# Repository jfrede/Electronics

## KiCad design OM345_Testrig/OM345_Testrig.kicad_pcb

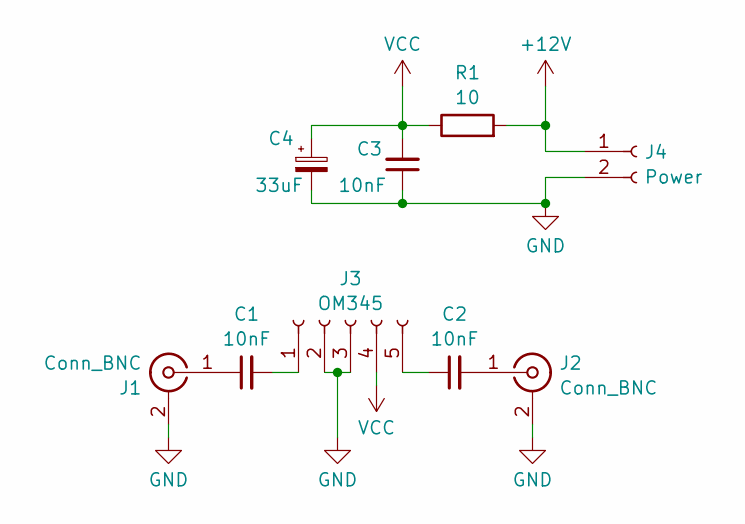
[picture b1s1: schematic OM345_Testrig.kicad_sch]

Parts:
C1, C2, C3: 10nF; C_0805_2012Metric_Pad1.18x1.45mm_HandSolder
C4: 33uF; CP_Radial_D5.0mm_P2.50mm
J1, J2: Conn_BNC; BNC_Amphenol_B6252HB-NPP3G-50_Horizontal
J3: OM345; PinSocket_1x05_P2.54mm_Vertical
J4: Power; PinHeader_1x02_P2.54mm_Vertical
R1: 10; R_0805_2012Metric_Pad1.20x1.40mm_HandSolder

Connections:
+12V: J4.1, R1.2
GND: C3.1, C4.2, J1.2 (Ext), J2.2 (Ext), J3.2, J3.3, J4.2
unnamed: C1.1, J1.1 (In)
unnamed: C2.2, J2.1 (In)
unnamed: C1.2, J3.1
unnamed: C2.1, J3.5
VCC: C3.2, C4.1, J3.4, R1.1

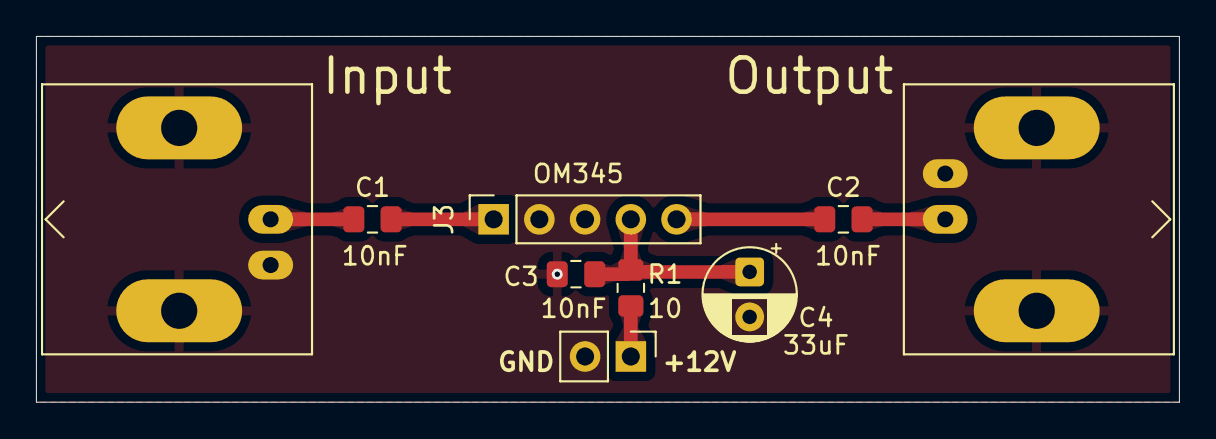
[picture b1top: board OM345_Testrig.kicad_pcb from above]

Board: 2 copper layers, 63.5 x 20.3 mm, 9 parts (0 on the bottom side), 7 nets.

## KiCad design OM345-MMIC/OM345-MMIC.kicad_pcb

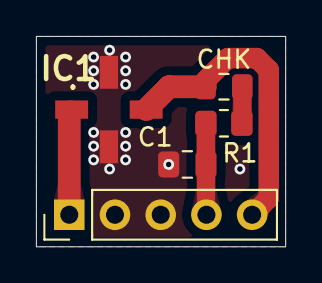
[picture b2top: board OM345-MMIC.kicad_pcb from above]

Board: 2 copper layers, 13.8 x 11.7 mm, 5 parts (0 on the bottom side), 5 nets.

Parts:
C1: 100n; C_0805_2012Metric_Pad1.18x1.45mm_HandSolder
CHK: 1k; L_0805_2012Metric_Pad1.15x1.40mm_HandSolder
IC1: MAR-7SM+; MAR7SM
J1: Conn_01x05_Pin; PinHeader_1x05_P2.54mm_Vertical
R1: 340; R_0805_2012Metric_Pad1.20x1.40mm_HandSolder

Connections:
GND: C1.1, IC1.2 (GND_1), IC1.4 (GND_2), J1.2, J1.3
unnamed: CHK.1, R1.2
unnamed: CHK.2, IC1.3 (RF-OUT_AND_DC-IN), J1.5
unnamed: IC1.1 (RF_IN), J1.1
unnamed: C1.2, J1.4, R1.1

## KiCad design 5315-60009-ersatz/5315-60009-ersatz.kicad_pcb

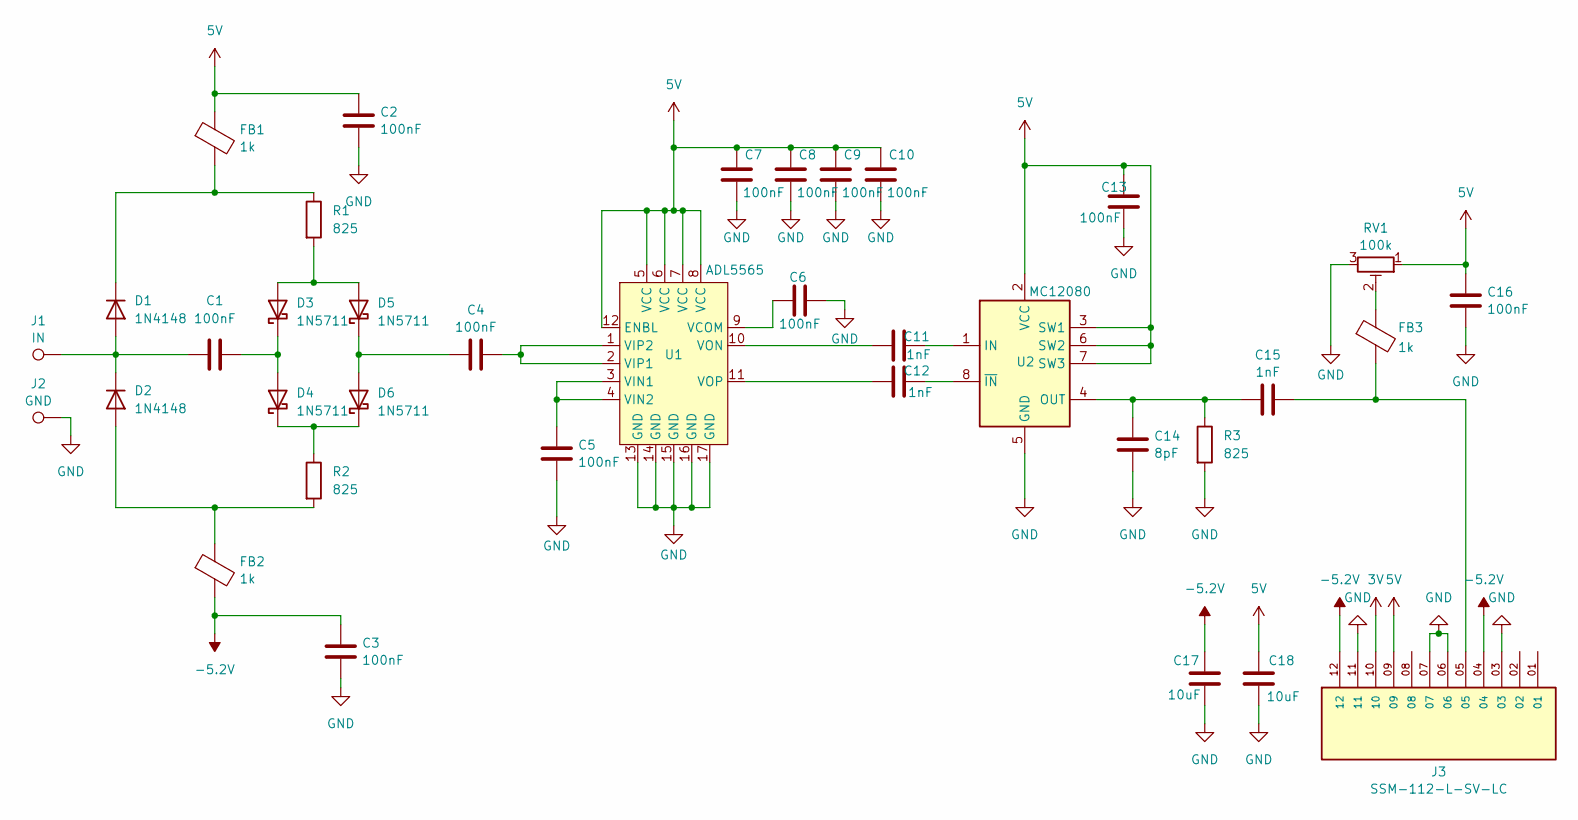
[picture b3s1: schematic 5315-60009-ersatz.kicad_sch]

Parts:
C1, C2, C3, C4, C5, C6, C7, C8, C9, C10, C13, C16: 100nF; C_0805_2012Metric
C11, C12, C15: 1nF; C_0805_2012Metric
C14: 8pF; C_0805_2012Metric
C17, C18: 10uF; R_1210_3225Metric
D1, D2: 1N4148; D_SOD-123F
D3, D4, D5, D6: 1N5711; D_SOD-123F
FB1, FB2, FB3: 1k; L_0805_2012Metric
J1: IN; TestPoint_Loop_D2.50mm_Drill1.0mm
J2: GND; TestPoint_Bridge_Pitch2.54mm_Drill1.0mm
J3: SSM-112-L-SV-LC; SAMTEC_SSM-112-L-SV-LC
R1, R2, R3: 825; R_0805_2012Metric
RV1: 100k; Potentiometer_Bourns_3314G_Vertical
U1: ADL5565; LFCSP-16-1EP_3x3mm_P0.5mm_EP1.6x1.6mm_ThermalVias
U2: MC12080; SOIC-8_3.9x4.9mm_P1.27mm

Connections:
3V: J3.10
5V: C2.1, C7.1, C8.1, C9.1, C10.1, C13.1, C16.1, C18.1, FB1.1, J3.09, RV1.1, U1.5 (VCC), U1.6 (VCC), U1.7 (VCC), U1.8 (VCC), U1.12 (ENBL), U2.2 (VCC), U2.3 (SW1), U2.6 (SW2), U2.7 (SW3)
-5.2V: C3.1, C17.1, FB2.2, J3.04, J3.12
GND: C2.2, C3.2, C5.2, C6.2, C7.2, C8.2, C9.2, C10.2, C13.2, C14.2, C16.2, C17.2, C18.2, J2.1, J3.03, J3.06, J3.07, J3.11, R3.2, RV1.3, U1.13 (GND), U1.14 (GND), U1.15 (GND), U1.16 (GND), U1.17 (GND), U2.5 (GND); also elsewhere on the board
unnamed: C15.2, FB3.2, J3.05
unnamed: C1.1, D1.2 (A), D2.1 (K), J1.1
unnamed: D1.1 (K), FB1.2, R1.1
unnamed: D2.2 (A), FB2.1, R2.2
unnamed: D3.2 (A), D5.2 (A), R1.2
unnamed: C1.2, D3.1 (K), D4.2 (A)
unnamed: D4.1 (K), D6.1 (K), R2.1
unnamed: C4.1, D5.1 (K), D6.2 (A)
unnamed 12: FB3.1, RV1.2; also elsewhere on the board
unnamed: C6.1, U1.9 (VCOM)
unnamed: C5.1, U1.3 (VIN1), U1.4 (VIN2)
unnamed: C4.2, U1.1 (VIP2), U1.2 (VIP1)
unnamed: C11.1, U1.10 (VON)
unnamed: C12.1, U1.11 (VOP)
unnamed: C11.2, U2.1 (IN)
unnamed: C14.1, C15.1, R3.1, U2.4 (OUT)
unnamed: C12.2, U2.8 (~IN)

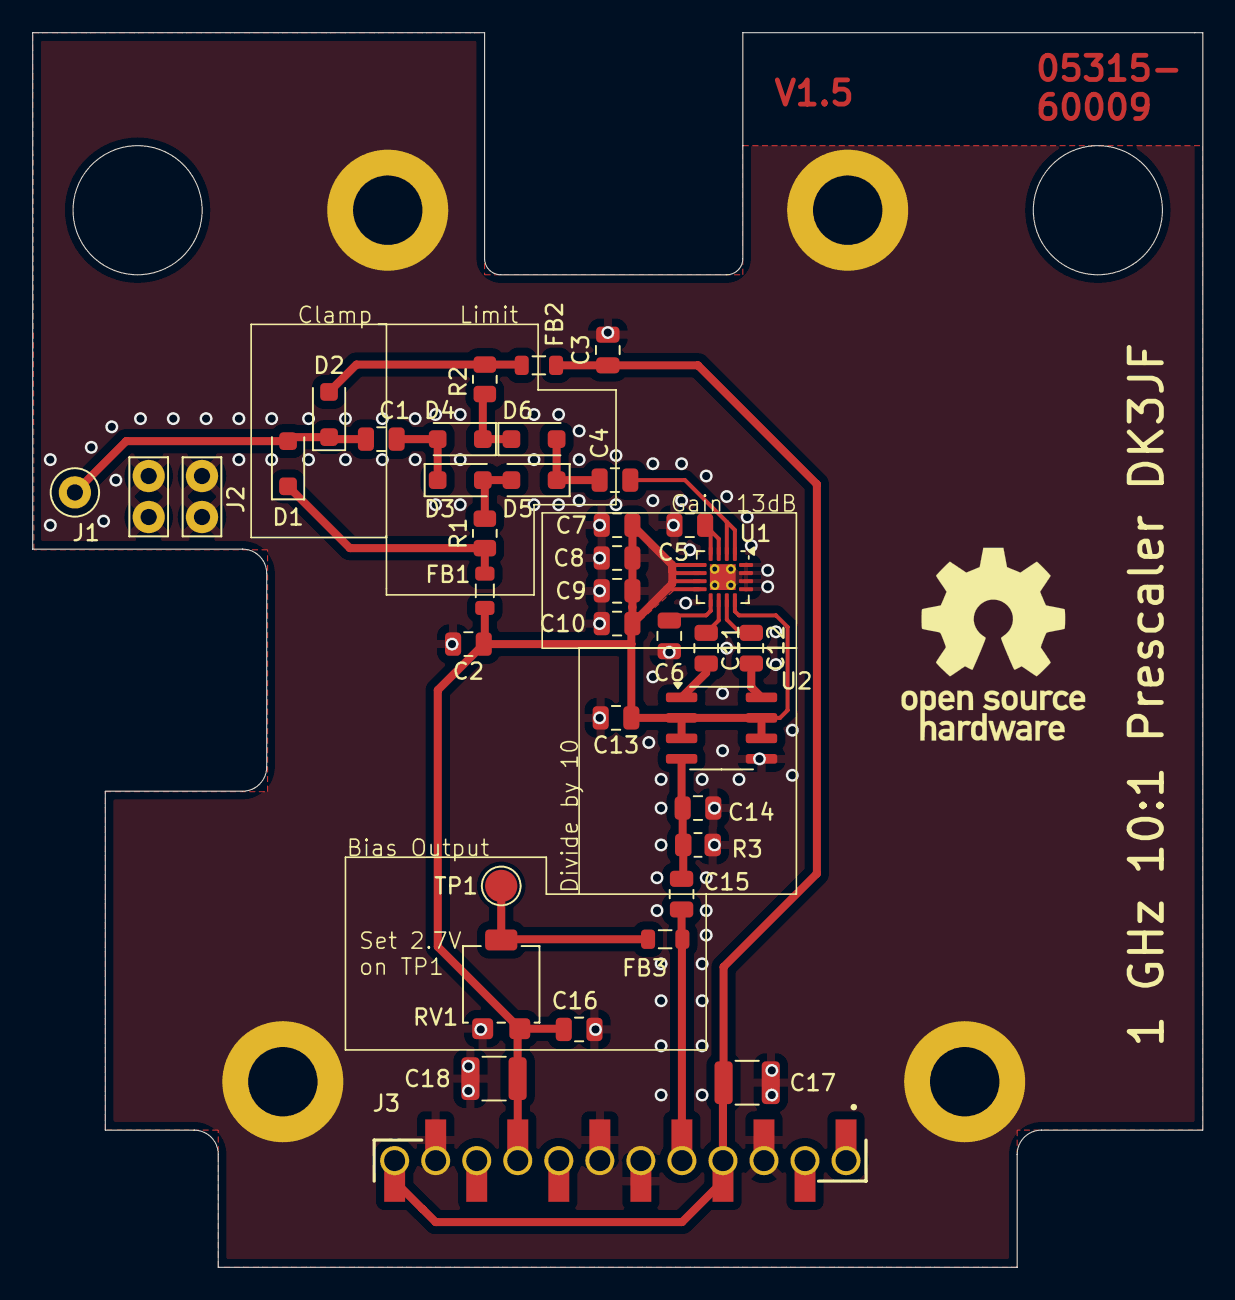
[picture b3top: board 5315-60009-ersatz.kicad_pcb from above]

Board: 2 copper layers, 72.5 x 76.5 mm, 38 parts (0 on the bottom side), 20 nets.

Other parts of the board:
J2#2: GND; TestPoint_Bridge_Pitch2.54mm_Drill1.0mm
TP1: TestPoint_Pad_D2.0mm

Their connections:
GND: J2#2.1; also elsewhere on the board
unnamed 12: TP1.1; also elsewhere on the board

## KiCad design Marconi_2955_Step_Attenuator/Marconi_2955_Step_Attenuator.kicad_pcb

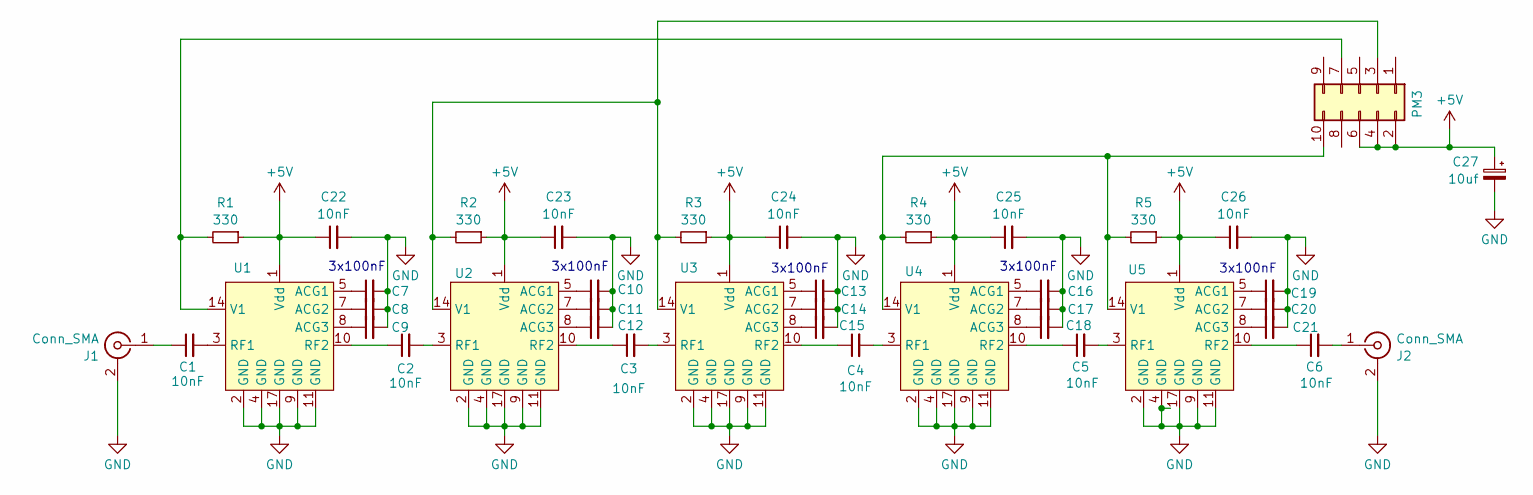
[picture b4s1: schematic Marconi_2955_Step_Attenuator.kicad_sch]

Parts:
C1, C2, C3, C4, C5, C6, C22, C23, C24, C25, C26: 10nF; C_0603_1608Metric
C7, C8, C9, C10, C11, C12, C13, C14, C15, C16, C17, C18, C19, C20, C21: 100nF; C_0603_1608Metric
C27: 10uf; CP_Radial_D6.3mm_P2.50mm
J1, J2: Conn_SMA; SMA_Wurth_60312002114503_Vertical
J3: PM3; PinHeader_2x05_P2.54mm_Vertical
R1, R2, R3, R4, R5: 330; R_0805_2012Metric
U1, U2, U3, U4, U5: QFN-16-1EP_3x3mm_P0.5mm_EP1.9x1.9mm

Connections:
+5V: C22.1, C23.1, C24.1, C25.1, C26.1, C27.1, J3.2, J3.4, J3.6, R1.1, R2.1, R3.1, R4.1, R5.1, U1.1 (Vdd), U2.1 (Vdd), U3.1 (Vdd), U4.1 (Vdd), U5.1 (Vdd)
GND: C7.2, C8.2, C9.2, C10.2, C11.2, C12.2, C13.2, C14.2, C15.2, C16.2, C17.2, C18.2, C19.2, C20.2, C21.2, C22.2, C23.2, C24.2, C25.2, C26.2, C27.2, J1.2 (Ext), J2.2 (Ext), U1.2 (GND), U1.4 (GND), U1.9 (GND), U1.11 (GND), U1.17 (GND), U2.2 (GND), U2.4 (GND), U2.9 (GND), U2.11 (GND), U2.17 (GND), U3.2 (GND), U3.4 (GND), U3.9 (GND), U3.11 (GND), U3.17 (GND), U4.2 (GND), U4.4 (GND), U4.9 (GND), U4.11 (GND), U4.17 (GND), U5.2 (GND), U5.4 (GND), U5.9 (GND), U5.11 (GND), U5.17 (GND)
unnamed: C1.1, J1.1 (In)
unnamed: C6.2, J2.1 (In)
unnamed: J3.3, R2.2, R3.2, U2.14 (V1), U3.14 (V1)
unnamed: J3.7, R1.2, U1.14 (V1)
unnamed: J3.10, R4.2, R5.2, U4.14 (V1), U5.14 (V1)
unnamed: C7.1, U1.5 (ACG1)
unnamed: C8.1, U1.7 (ACG2)
unnamed: C9.1, U1.8 (ACG3)
unnamed: C1.2, U1.3 (RF1)
unnamed: C2.1, U1.10 (RF2)
unnamed: C10.1, U2.5 (ACG1)
unnamed: C11.1, U2.7 (ACG2)
unnamed: C12.1, U2.8 (ACG3)
unnamed: C2.2, U2.3 (RF1)
unnamed: C3.1, U2.10 (RF2)
unnamed: C13.1, U3.5 (ACG1)
unnamed: C14.1, U3.7 (ACG2)
unnamed: C15.1, U3.8 (ACG3)
unnamed: C3.2, U3.3 (RF1)
unnamed: C4.1, U3.10 (RF2)
unnamed: C16.1, U4.5 (ACG1)
unnamed: C17.1, U4.7 (ACG2)
unnamed: C18.1, U4.8 (ACG3)
unnamed: C4.2, U4.3 (RF1)
unnamed: C5.1, U4.10 (RF2)
unnamed: C19.1, U5.5 (ACG1)
unnamed: C20.1, U5.7 (ACG2)
unnamed: C21.1, U5.8 (ACG3)
unnamed: C5.2, U5.3 (RF1)
unnamed: C6.1, U5.10 (RF2)

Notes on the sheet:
3x100nF

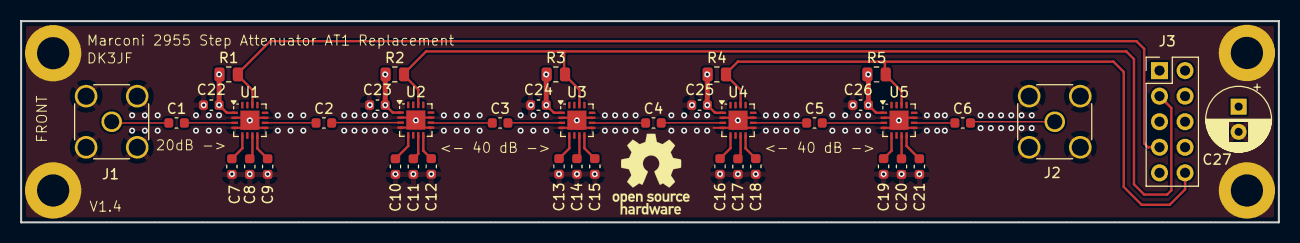
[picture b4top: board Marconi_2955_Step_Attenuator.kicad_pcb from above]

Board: 4 copper layers, 125.0 x 20.0 mm, 40 parts (0 on the bottom side), 32 nets.

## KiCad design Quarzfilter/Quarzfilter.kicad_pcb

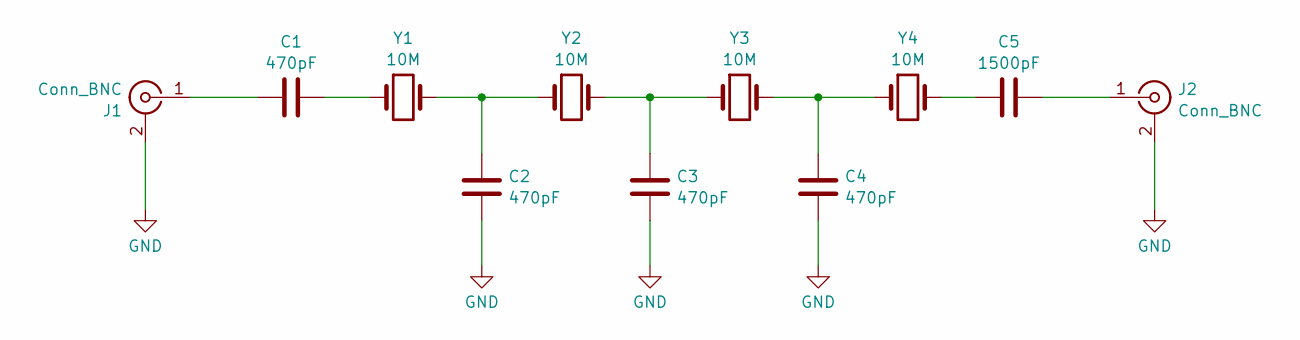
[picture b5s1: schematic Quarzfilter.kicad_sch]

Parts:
C1, C2, C3, C4: 470pF; C_0805_2012Metric
C5: 1500pF; C_0805_2012Metric
J1, J2: Conn_BNC; BNC_Amphenol_B6252HB-NPP3G-50_Horizontal
Y1, Y2, Y3, Y4: 10M; Crystal_HC49-U_Vertical

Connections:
GND: C2.2, C3.1, C4.1, J1.2 (Ext), J2.2 (Ext)
unnamed: C1.2, Y1.1
unnamed: C2.1, Y1.2, Y2.1
unnamed: C3.2, Y2.2, Y3.1
unnamed: C4.2, Y3.2, Y4.1
unnamed: C5.1, Y4.2
unnamed: C1.1, J1.1 (In)
unnamed: C5.2, J2.1 (In)

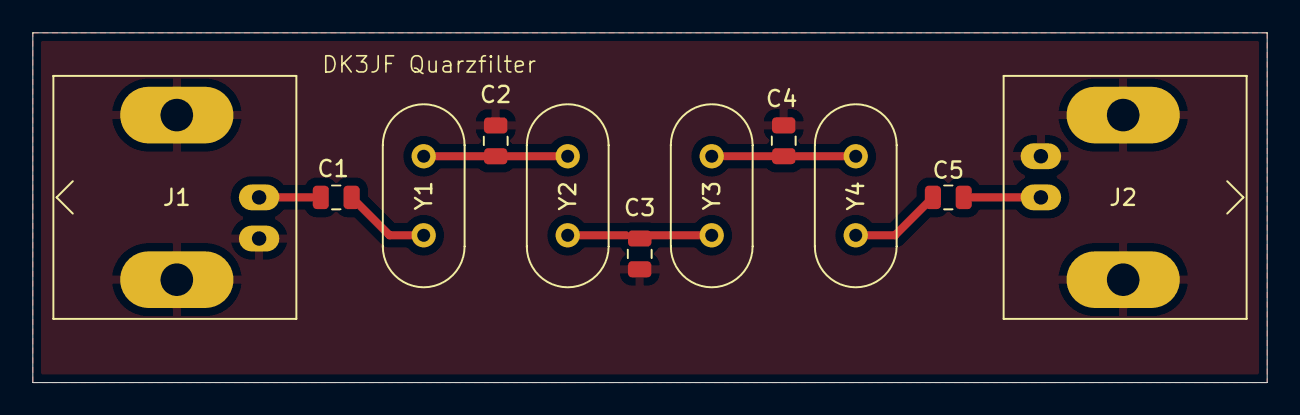
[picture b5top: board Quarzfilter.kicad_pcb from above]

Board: 2 copper layers, 76.2 x 21.6 mm, 11 parts (0 on the bottom side), 8 nets.

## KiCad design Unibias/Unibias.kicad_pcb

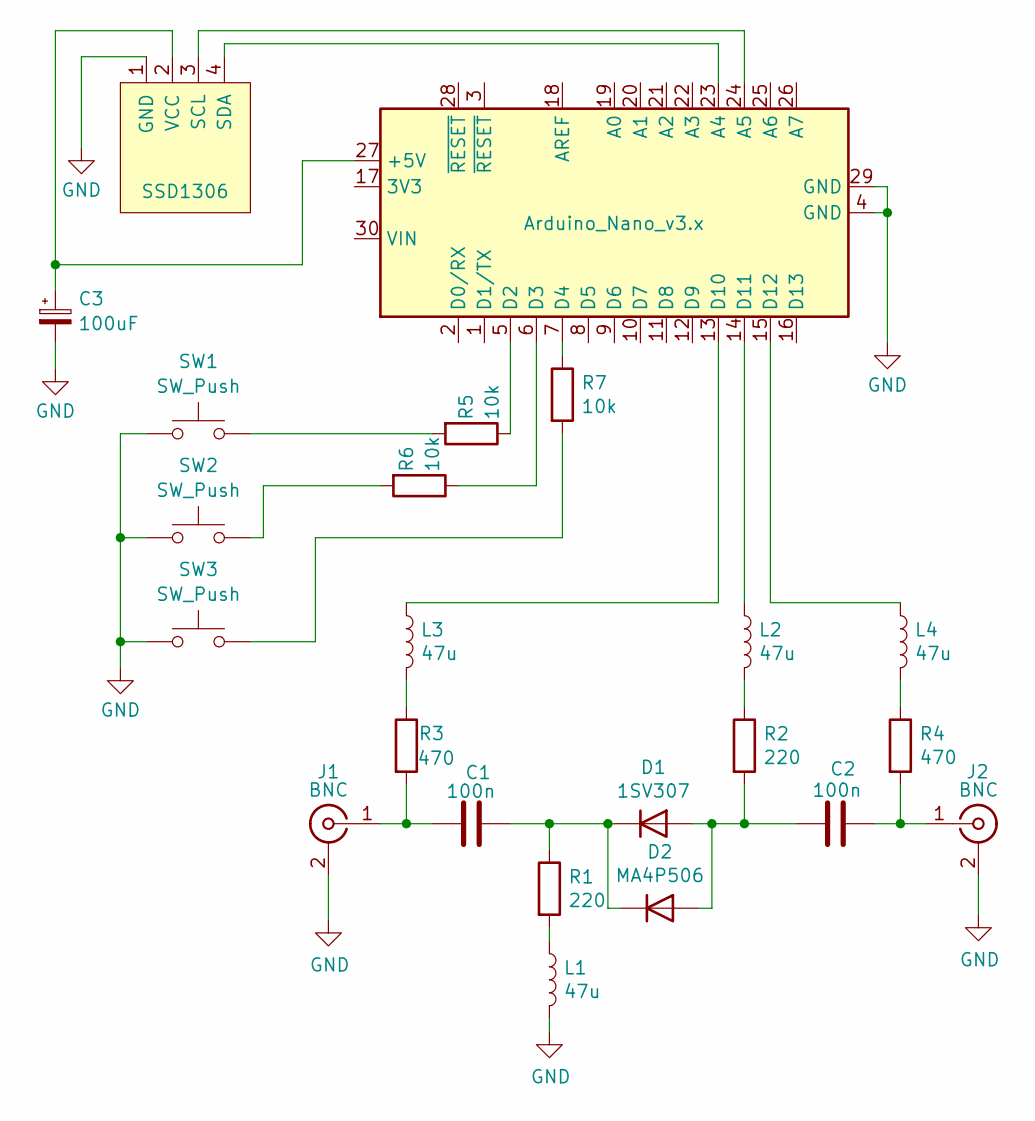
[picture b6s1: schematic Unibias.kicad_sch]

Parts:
A1: Arduino_Nano_v3.x; Arduino_Nano
Brd1: SSD1306; 128x64OLED
C1, C2: 100n; C_0805_2012Metric
C3: 100uF; CP_Elec_6.3x7.7
D1: 1SV307; D_SOD-323
D2: MA4P506; D_MELF
J1, J2: BNC; BNC_Amphenol_B6252HB-NPP3G-50_Horizontal
L1, L2, L3, L4: 47u; L_0805_2012Metric
R1, R2: 220; R_0805_2012Metric
R3, R4: 470; R_0805_2012Metric
R5, R6, R7: 10k; R_0805_2012Metric
SW1, SW2, SW3: SW_Push; SW_PUSH_6mm

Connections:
GND: A1.4 (GND), A1.29 (GND), Brd1.1 (GND), C3.2, J1.2 (Ext), J2.2 (Ext), L1.2, SW1.1, SW2.1, SW3.1
unnamed: A1.27 (+5V), Brd1.2 (VCC), C3.1
unnamed: A1.23 (A4), Brd1.4 (SDA)
unnamed: A1.24 (A5), Brd1.3 (SCL)
unnamed: A1.5 (D2), R5.1
unnamed: A1.6 (D3), R6.1
unnamed: A1.7 (D4), R7.1
unnamed: A1.13 (D10), L3.1
unnamed: A1.14 (D11), L2.1
unnamed: A1.15 (D12), L4.1
unnamed: C2.2, D1.2 (A), D2.2 (A), R2.2
unnamed: C1.1, D1.1 (K), D2.1 (K), R1.1
unnamed: C1.2, J1.1 (In), R3.2
unnamed: C2.1, J2.1 (In), R4.2
unnamed: L1.1, R1.2
unnamed: L2.2, R2.1
unnamed: L3.2, R3.1
unnamed: L4.2, R4.1
unnamed: R5.2, SW1.2
unnamed: R6.2, SW2.2
unnamed: R7.2, SW3.2

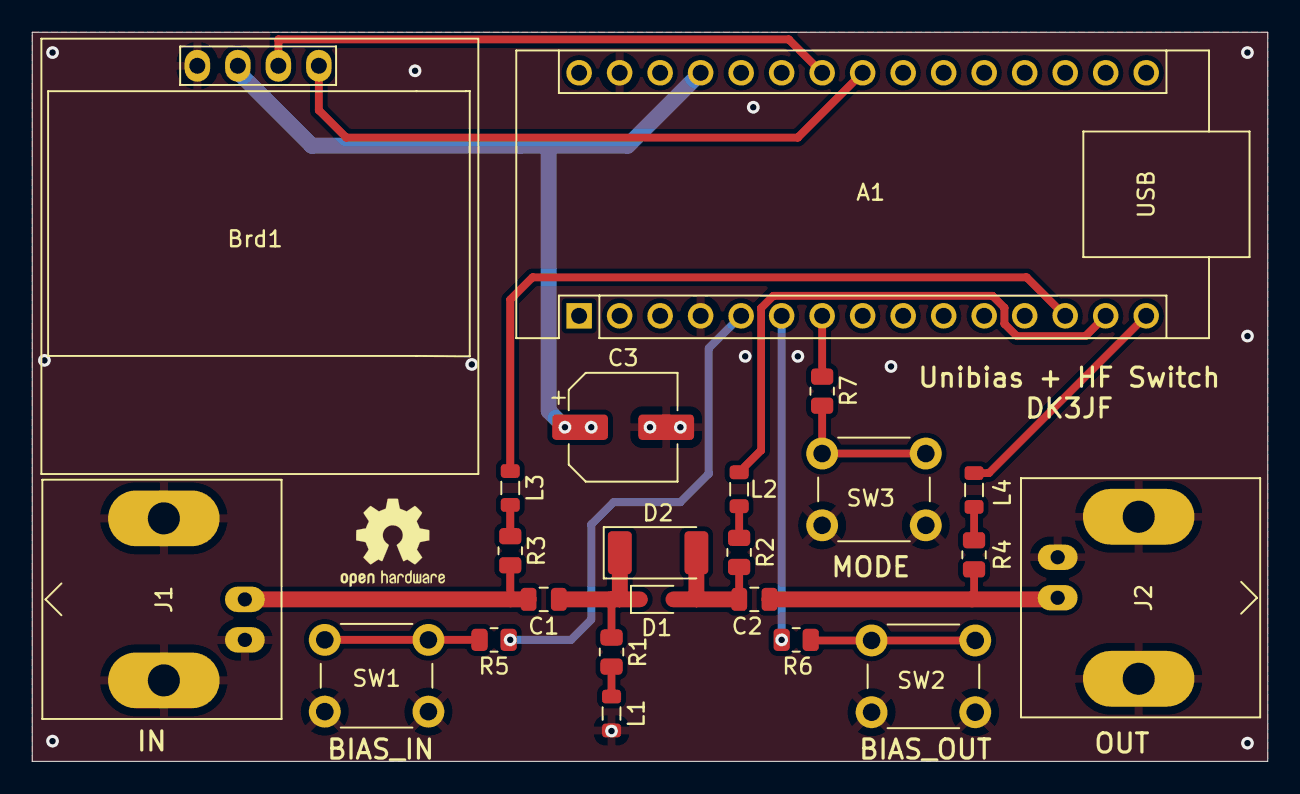
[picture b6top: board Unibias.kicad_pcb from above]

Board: 2 copper layers, 77.5 x 45.7 mm, 23 parts (0 on the bottom side), 21 nets.

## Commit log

2024-05-18 add Marconi_2955_Step_Attenuator
2024-05-18 add Unibiad add Quarzfilter
2024-12-21 add 5315-60009-ersatz
2026-02-06 add OM345 MMIC
